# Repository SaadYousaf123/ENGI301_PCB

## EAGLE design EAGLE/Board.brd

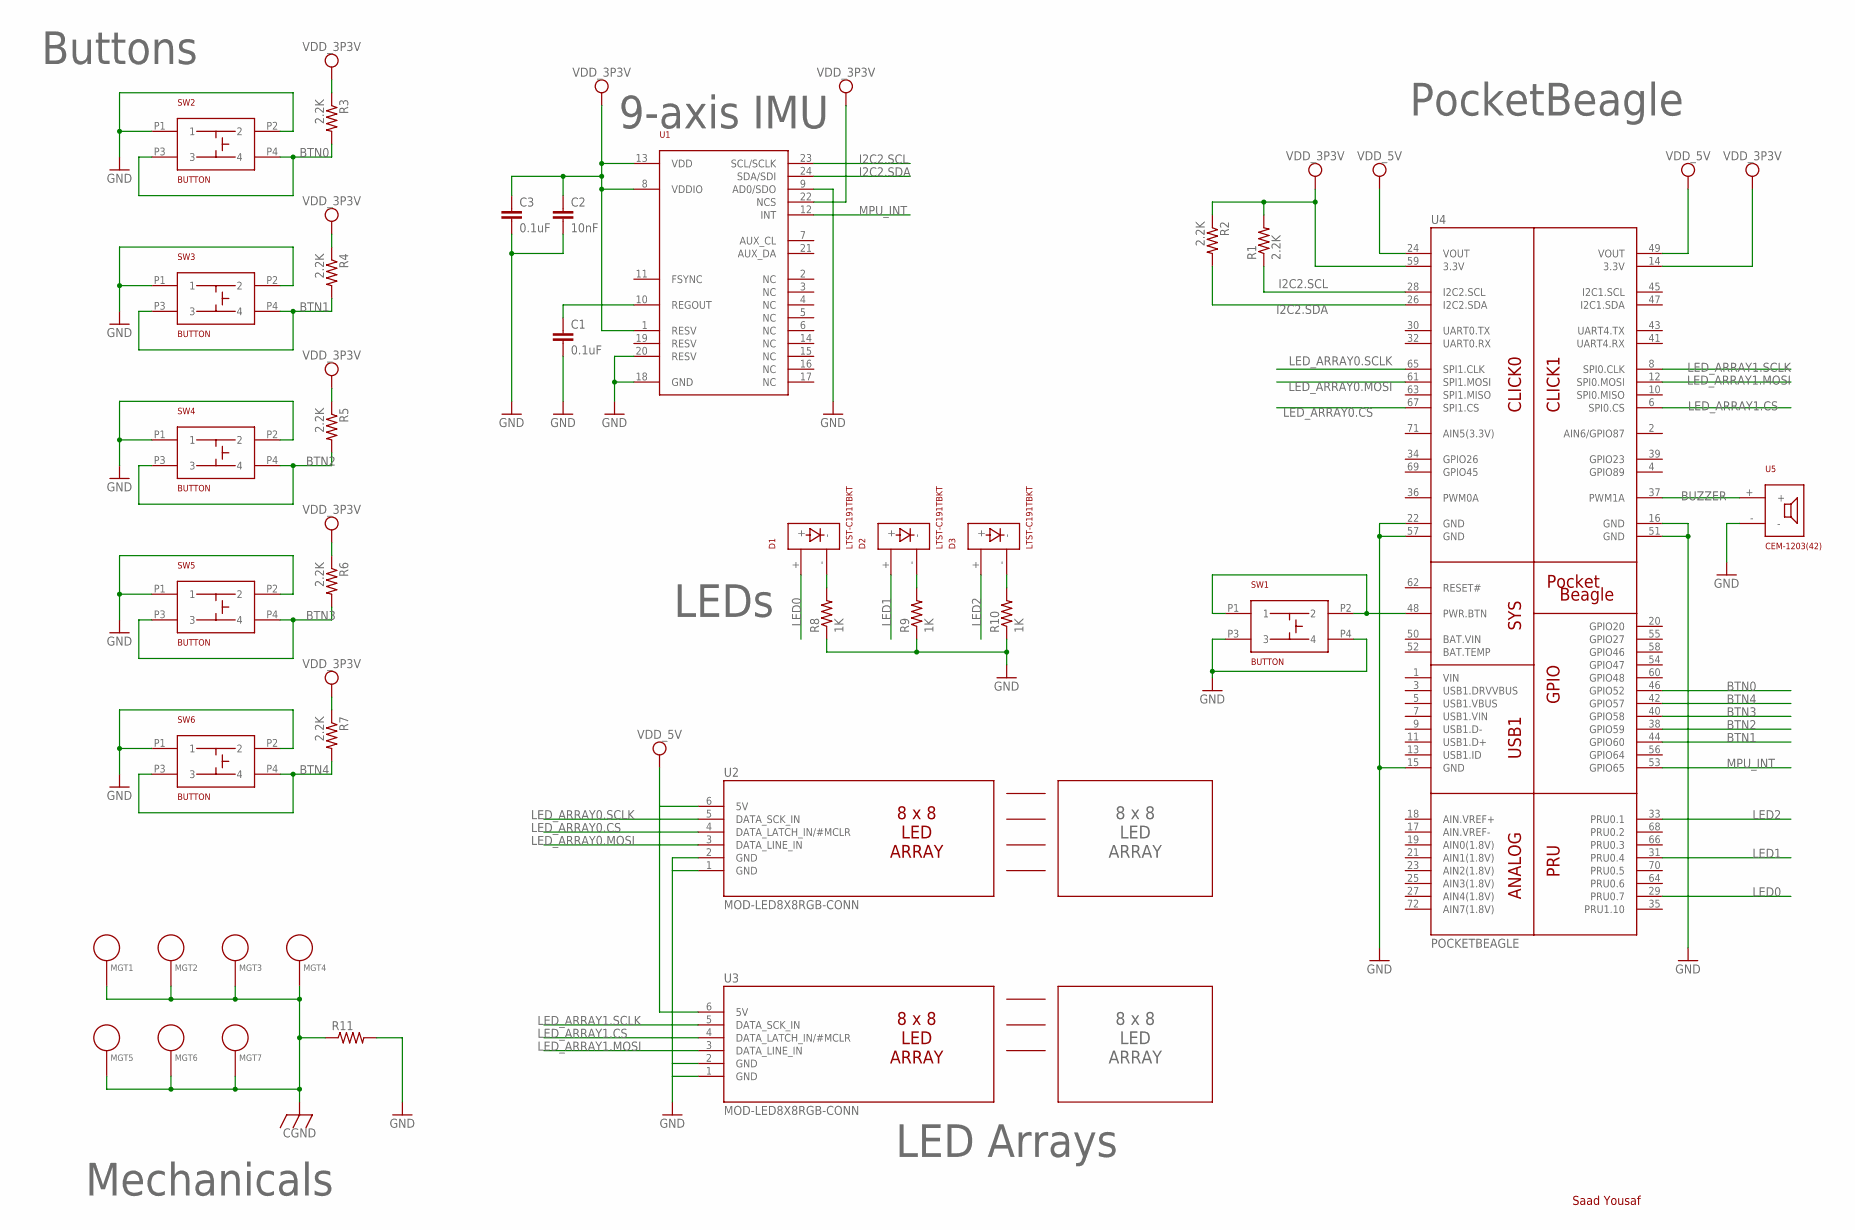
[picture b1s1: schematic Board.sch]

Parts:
C1, C3: 0.1uF; C0603
C2: 10nF; C0603
D1, D2, D3: LTST-C191TBKT; SMD-LED
MGT1, MGT2, MGT3, MGT4, MGT5, MGT6, MGT7: MOUNTING_HOLE
R1, R2, R3, R4, R5, R6, R7: 2.2K; R0603
R8, R9, R10: 1K; R0603
R11: R_R0603; R0603
SW1, SW2, SW3, SW4, SW5, SW6: BUTTON; BTN
U1: MPU-9250; QFN-3MMX3MM
U2, U3: MOD-LED8X8RGB-CONN; FE06W
U4: POCKETBEAGLE
U5: CEM-1203(42)

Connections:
BTN0: R3.2, SW2.P3 (3), SW2.P4 (4), U4.46 (GPIO52)
BTN1: R4.2, SW3.P3 (3), SW3.P4 (4), U4.44 (GPIO60)
BTN2: R5.2, SW4.P3 (3), SW4.P4 (4), U4.38 (GPIO59)
BTN3: R6.2, SW5.P3 (3), SW5.P4 (4), U4.40 (GPIO58)
BTN4: R7.2, SW6.P3 (3), SW6.P4 (4), U4.42 (GPIO57)
BUZZER: U4.37 (PWM1A), U5.+
CGND: MGT1.P$1, MGT2.P$1, MGT3.P$1, MGT4.P$1, MGT5.P$1, MGT6.P$1, MGT7.P$1, R11.1
GND: C1.2, C2.2, C3.2, R8.1, R9.1, R10.1, R11.2, SW1.P3 (3), SW1.P4 (4), SW2.P1 (1), SW2.P2 (2), SW3.P1 (1), SW3.P2 (2), SW4.P1 (1), SW4.P2 (2), SW5.P1 (1), SW5.P2 (2), SW6.P1 (1), SW6.P2 (2), U1.9 (AD0/SDO), U1.18 (GND), U1.20 (RESV), U2.1 (GND), U2.2 (GND), U3.1 (GND), U3.2 (GND), U4.15 (GND), U4.16 (GND), U4.22 (GND), U4.51 (GND), U4.57 (GND), U5.-
I2C2.SCL: R1.1, U1.23 (SCL/SCLK), U4.28 (I2C2.SCL)
I2C2.SDA: R2.2, U1.24 (SDA/SDI), U4.26 (I2C2.SDA)
LED0: D1.+, U4.29 (PRU0.7)
LED1: D2.+, U4.31 (PRU0.4)
LED2: D3.+, U4.33 (PRU0.1)
LED_ARRAY0.CS: U2.4 (DATA_LATCH_IN/#MCLR), U4.67 (SPI1.CS)
LED_ARRAY0.MOSI: U2.3 (DATA_LINE_IN), U4.61 (SPI1.MOSI)
LED_ARRAY0.SCLK: U2.5 (DATA_SCK_IN), U4.65 (SPI1.CLK)
LED_ARRAY1.CS: U3.4 (DATA_LATCH_IN/#MCLR), U4.6 (SPI0.CS)
LED_ARRAY1.MOSI: U3.3 (DATA_LINE_IN), U4.12 (SPI0.MOSI)
LED_ARRAY1.SCLK: U3.5 (DATA_SCK_IN), U4.8 (SPI0.CLK)
MPU_INT: U1.12 (INT), U4.53 (GPIO65)
unnamed: C1.1, U1.10 (REGOUT)
unnamed: SW1.P1 (1), SW1.P2 (2), U4.48 (PWR.BTN)
unnamed: D1.-, R8.2
unnamed: D2.-, R9.2
unnamed: D3.-, R10.2
SYS_VDD1_5V: C2.1, C3.1, R1.2, R2.1, R3.1, R4.1, R5.1, R6.1, R7.1, U1.1 (RESV), U1.8 (VDDIO), U1.13 (VDD), U1.22 (NCS), U2.6 (5V), U3.6 (5V), U4.14 (3.3V), U4.24 (VOUT), U4.49 (VOUT), U4.59 (3.3V)

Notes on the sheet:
Saad Yousaf
8 x 8 LED ARRAY
PocketBeagle
9-axis IMU
LEDs
LED Arrays
Mechanicals
Buttons

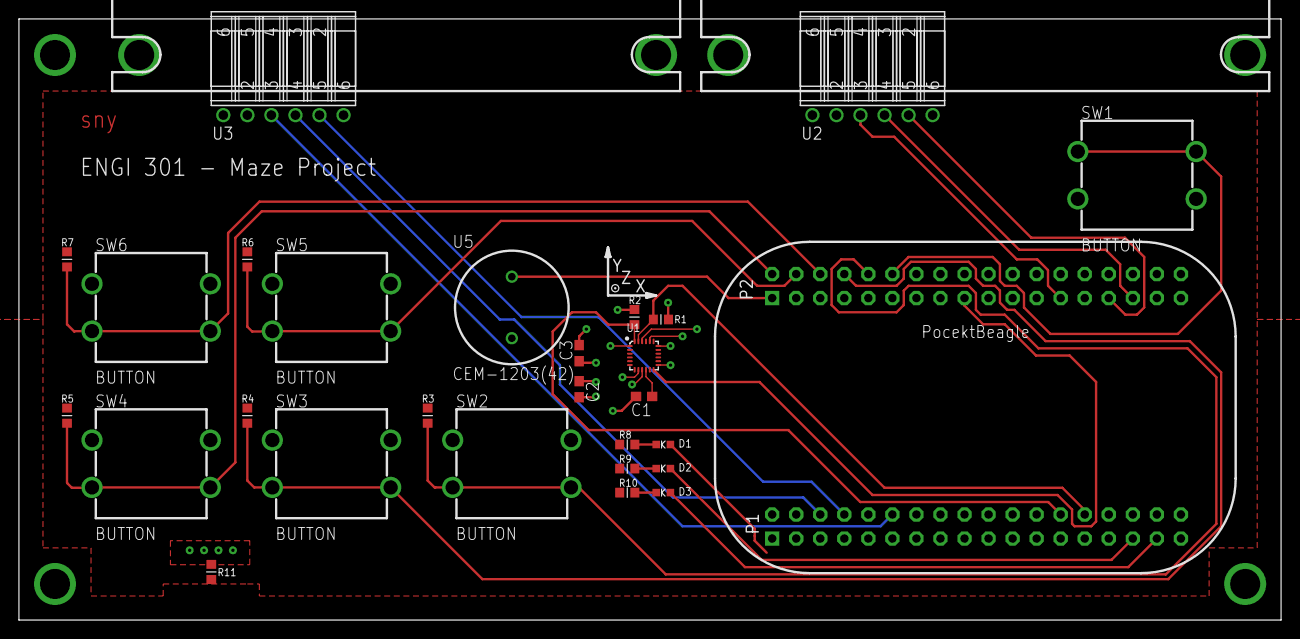
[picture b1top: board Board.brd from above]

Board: 4 copper layers, 133.3 x 63.5 mm, 40 parts (0 on the bottom side), 26 nets.

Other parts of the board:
U$1, U$2, U$3, U$4: MOD-LED8X8RGB
U$5: XYZ-LABEL

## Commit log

2018-04-10 Create EAGLE
2018-04-22 Deleted EAGLE file.
2018-04-22 whatever you want
